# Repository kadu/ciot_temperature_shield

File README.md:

Temperature Shield
=======================

A temperature shield (DHTx) that send informations to CIOT server.

On eagle directory has a sch and brd for schematic and board ;)

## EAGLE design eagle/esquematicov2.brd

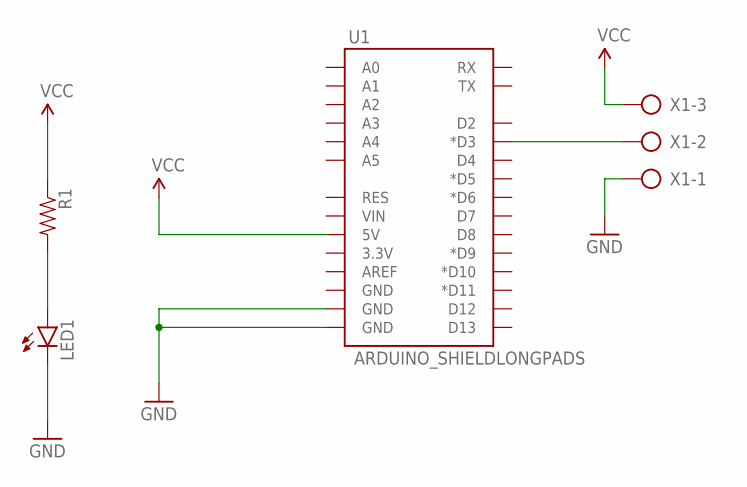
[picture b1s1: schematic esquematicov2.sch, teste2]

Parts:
LED1: LED5MM
R1: RESISTORPTH-1/4W-VERT; AXIAL-0.1
U1: ARDUINO_SHIELDLONGPADS; DUEMILANOVE_SHIELD_LONGPADS
X1: AK500/3-H

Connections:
GND: LED1.K (C), U1.GND@0 (GND), U1.GND@1 (GND), X1.1
unnamed: LED1.A, R1.P$2 (2)
unnamed: U1.D3 (*D3), X1.2
VCC: R1.P$1 (1), U1.5V, X1.3

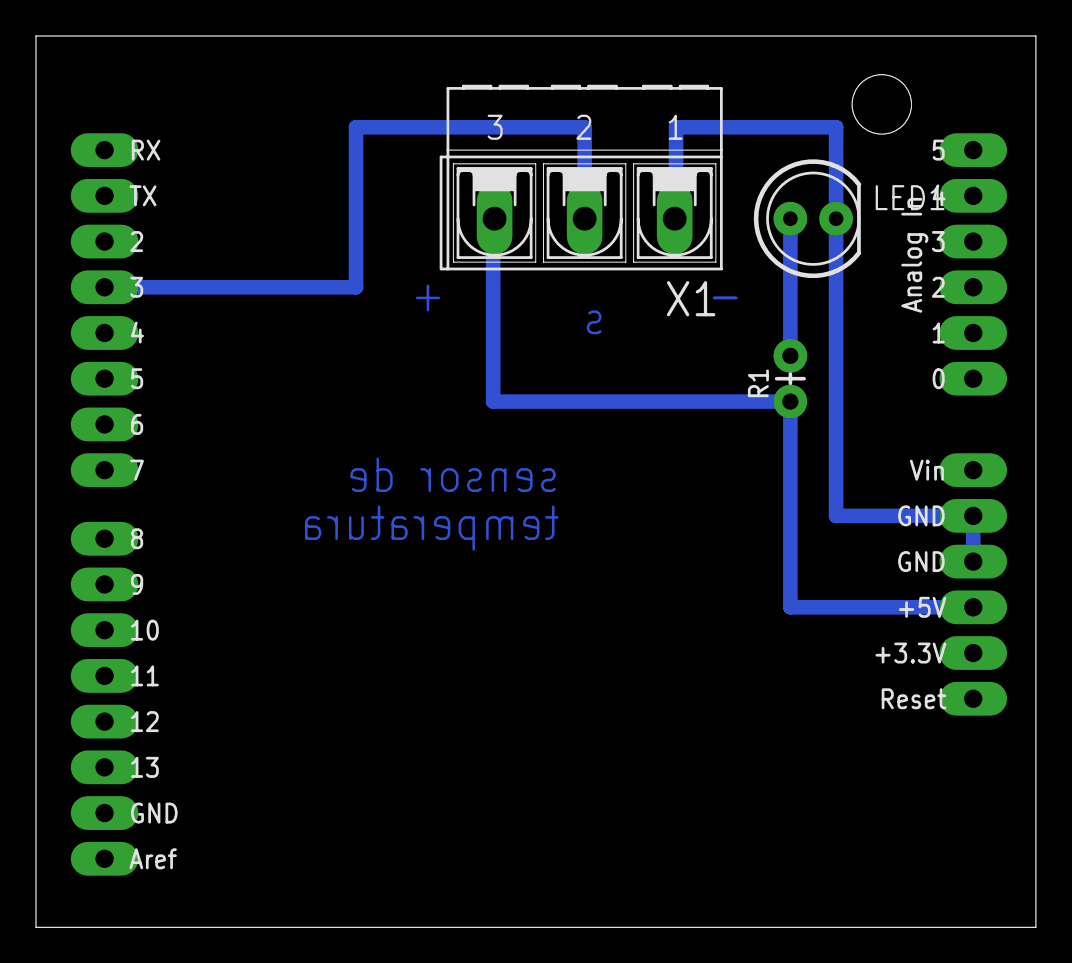
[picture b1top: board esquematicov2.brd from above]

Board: 2 copper layers, 55.5 x 49.5 mm, 4 parts (0 on the bottom side), 4 nets.

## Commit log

2014-12-08 Starting the work ;)
2014-12-08 Starting work 2.0

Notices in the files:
parts and their libraries:
SparkFun-LED: Licensing: Creative Commons ShareAlike 4.0 International - https://creativecommons.org/licenses/by-sa/4.0
